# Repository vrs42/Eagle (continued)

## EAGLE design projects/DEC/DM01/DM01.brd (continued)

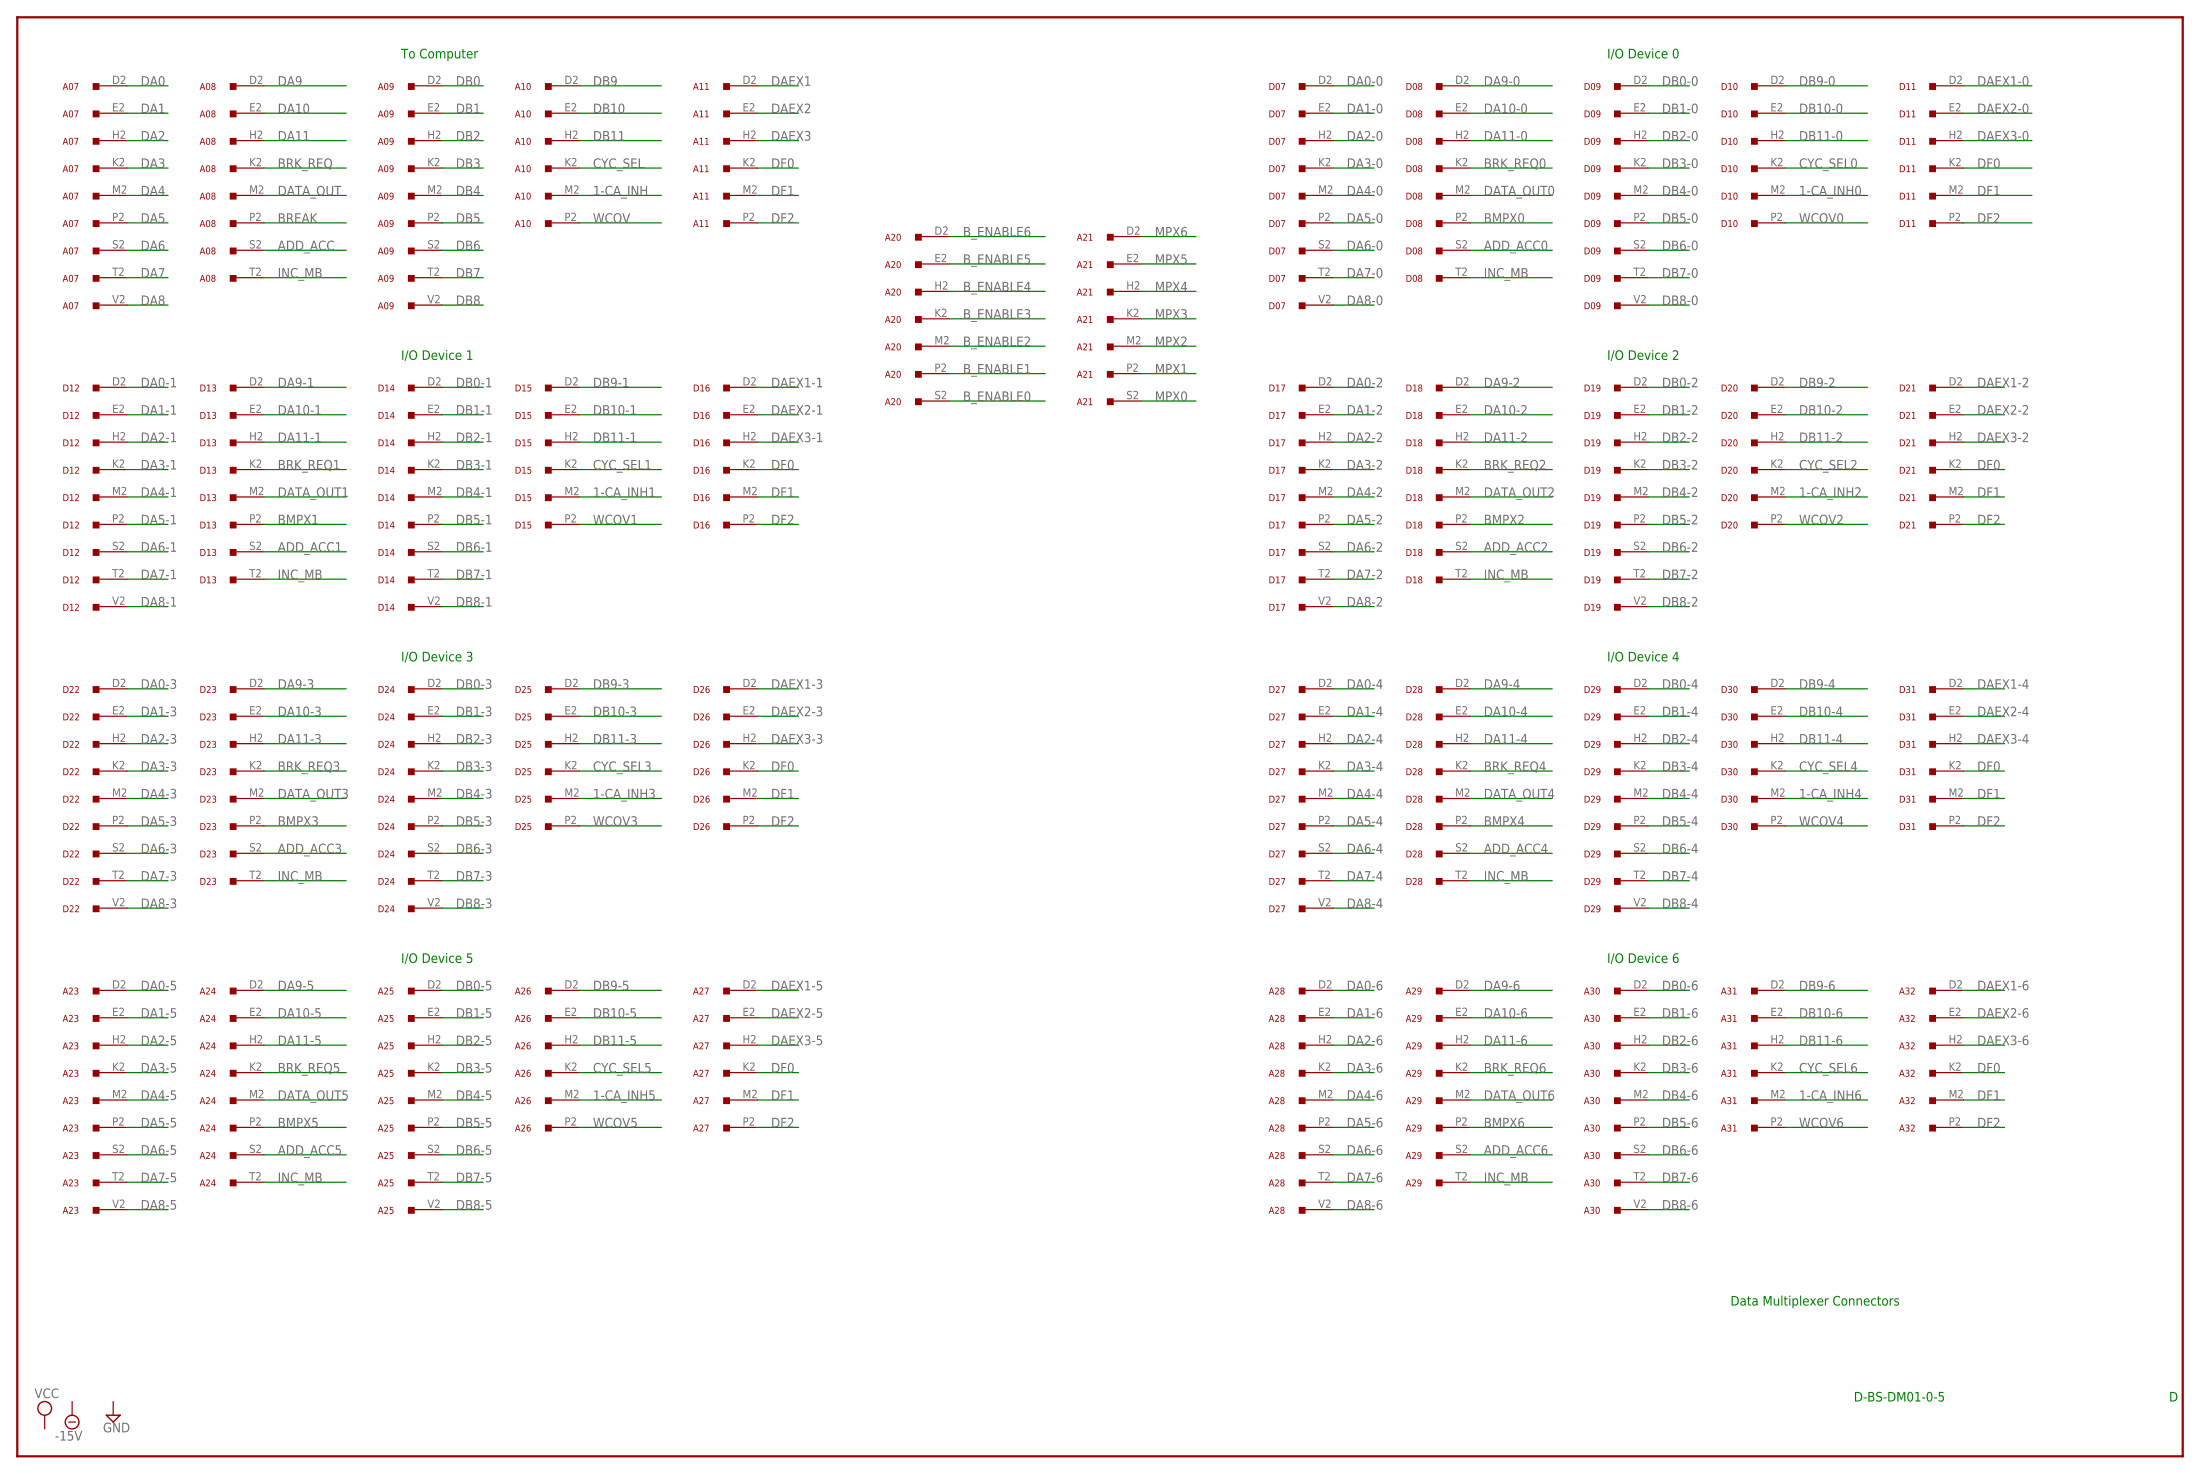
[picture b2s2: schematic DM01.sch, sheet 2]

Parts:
A07, A08, A09, A10, A11, A20, A21, A23, A24, A25, A26, A27, A28, A29, A30, A31, A32: W021S; H807S
D07, D08, D09, D10, D11, D12, D13, D14, D15, D16, D17, D18, D19, D20, D21, D22, D23, D24, D25, D26, D27, D28, D29, D30, D31: W021S; H807S

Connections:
1-CA_INH: A10.M2; also elsewhere on the board
1-CA_INH0: D10.M2; also elsewhere on the board
1-CA_INH1: D15.M2; also elsewhere on the board
1-CA_INH2: D20.M2; also elsewhere on the board
1-CA_INH3: D25.M2; also elsewhere on the board
1-CA_INH4: D30.M2; also elsewhere on the board
1-CA_INH5: A26.M2; also elsewhere on the board
1-CA_INH6: A31.M2; also elsewhere on the board
ADD_ACC: A08.S2; also elsewhere on the board
ADD_ACC0: D08.S2; also elsewhere on the board
ADD_ACC1: D13.S2; also elsewhere on the board
ADD_ACC2: D18.S2; also elsewhere on the board
ADD_ACC3: D23.S2; also elsewhere on the board
ADD_ACC4: D28.S2; also elsewhere on the board
ADD_ACC5: A24.S2; also elsewhere on the board
ADD_ACC6: A29.S2; also elsewhere on the board
BMPX0: D08.P2; also elsewhere on the board
BMPX1: D13.P2; also elsewhere on the board
BMPX2: D18.P2; also elsewhere on the board
BMPX3: D23.P2; also elsewhere on the board
BMPX4: D28.P2; also elsewhere on the board
BMPX5: A24.P2; also elsewhere on the board
BMPX6: A29.P2; also elsewhere on the board
BREAK: A08.P2; also elsewhere on the board
BRK_REQ: A08.K2; also elsewhere on the board
BRK_REQ0: D08.K2; also elsewhere on the board
BRK_REQ1: D13.K2; also elsewhere on the board
BRK_REQ2: D18.K2; also elsewhere on the board
BRK_REQ3: D23.K2; also elsewhere on the board
BRK_REQ4: D28.K2; also elsewhere on the board
BRK_REQ5: A24.K2; also elsewhere on the board
BRK_REQ6: A29.K2; also elsewhere on the board
B_ENABLE0: A20.S2; also elsewhere on the board
B_ENABLE1: A20.P2; also elsewhere on the board
B_ENABLE2: A20.M2; also elsewhere on the board
B_ENABLE3: A20.K2; also elsewhere on the board
B_ENABLE4: A20.H2; also elsewhere on the board
B_ENABLE5: A20.E2; also elsewhere on the board
B_ENABLE6: A20.D2; also elsewhere on the board
CYC_SEL: A10.K2; also elsewhere on the board
CYC_SEL0: D10.K2; also elsewhere on the board
CYC_SEL1: D15.K2; also elsewhere on the board
CYC_SEL2: D20.K2; also elsewhere on the board
CYC_SEL3: D25.K2; also elsewhere on the board
CYC_SEL4: D30.K2; also elsewhere on the board
CYC_SEL5: A26.K2; also elsewhere on the board
CYC_SEL6: A31.K2; also elsewhere on the board
DA0: A07.D2; also elsewhere on the board
DA0-0: D07.D2; also elsewhere on the board
DA0-1: D12.D2; also elsewhere on the board
DA0-2: D17.D2; also elsewhere on the board
DA0-3: D22.D2; also elsewhere on the board
DA0-4: D27.D2; also elsewhere on the board
DA0-5: A23.D2; also elsewhere on the board
DA0-6: A28.D2; also elsewhere on the board
DA1: A07.E2; also elsewhere on the board
DA1-0: D07.E2; also elsewhere on the board
DA1-1: D12.E2; also elsewhere on the board
DA1-2: D17.E2; also elsewhere on the board
DA1-3: D22.E2; also elsewhere on the board
DA1-4: D27.E2; also elsewhere on the board
DA1-5: A23.E2; also elsewhere on the board
DA1-6: A28.E2; also elsewhere on the board
DA2: A07.H2; also elsewhere on the board
DA2-0: D07.H2; also elsewhere on the board
DA2-1: D12.H2; also elsewhere on the board
DA2-2: D17.H2; also elsewhere on the board
DA2-3: D22.H2; also elsewhere on the board
DA2-4: D27.H2; also elsewhere on the board
DA2-5: A23.H2; also elsewhere on the board
DA2-6: A28.H2; also elsewhere on the board
DA3: A07.K2; also elsewhere on the board
DA3-0: D07.K2; also elsewhere on the board
DA3-1: D12.K2; also elsewhere on the board
DA3-2: D17.K2; also elsewhere on the board
DA3-3: D22.K2; also elsewhere on the board
DA3-4: D27.K2; also elsewhere on the board
DA3-5: A23.K2; also elsewhere on the board
DA3-6: A28.K2; also elsewhere on the board
DA4: A07.M2; also elsewhere on the board
DA4-0: D07.M2; also elsewhere on the board
DA4-1: D12.M2; also elsewhere on the board
DA4-2: D17.M2; also elsewhere on the board
DA4-3: D22.M2; also elsewhere on the board
DA4-4: D27.M2; also elsewhere on the board
DA4-5: A23.M2; also elsewhere on the board
DA4-6: A28.M2; also elsewhere on the board
DA5: A07.P2; also elsewhere on the board
DA5-0: D07.P2; also elsewhere on the board
DA5-1: D12.P2; also elsewhere on the board
DA5-2: D17.P2; also elsewhere on the board
DA5-3: D22.P2; also elsewhere on the board
DA5-4: D27.P2; also elsewhere on the board
DA5-5: A23.P2; also elsewhere on the board
DA5-6: A28.P2; also elsewhere on the board
DA6: A07.S2; also elsewhere on the board
DA6-0: D07.S2; also elsewhere on the board
DA6-1: D12.S2; also elsewhere on the board
DA6-2: D17.S2; also elsewhere on the board
DA6-3: D22.S2; also elsewhere on the board
DA6-4: D27.S2; also elsewhere on the board
DA6-5: A23.S2; also elsewhere on the board
DA6-6: A28.S2; also elsewhere on the board
DA7: A07.T2; also elsewhere on the board
DA7-0: D07.T2; also elsewhere on the board
DA7-1: D12.T2; also elsewhere on the board
DA7-2: D17.T2; also elsewhere on the board
DA7-3: D22.T2; also elsewhere on the board
DA7-4: D27.T2; also elsewhere on the board
DA7-5: A23.T2; also elsewhere on the board
DA7-6: A28.T2; also elsewhere on the board
DA8: A07.V2; also elsewhere on the board
DA8-0: D07.V2; also elsewhere on the board
DA8-1: D12.V2; also elsewhere on the board
DA8-2: D17.V2; also elsewhere on the board
DA8-3: D22.V2; also elsewhere on the board
DA8-4: D27.V2; also elsewhere on the board
DA8-5: A23.V2; also elsewhere on the board
DA8-6: A28.V2; also elsewhere on the board
DA9: A08.D2; also elsewhere on the board
DA9-0: D08.D2; also elsewhere on the board
DA9-1: D13.D2; also elsewhere on the board
DA9-2: D18.D2; also elsewhere on the board
DA9-3: D23.D2; also elsewhere on the board
DA9-4: D28.D2; also elsewhere on the board
DA9-5: A24.D2; also elsewhere on the board
DA9-6: A29.D2; also elsewhere on the board
DA10: A08.E2; also elsewhere on the board
DA10-0: D08.E2; also elsewhere on the board
DA10-1: D13.E2; also elsewhere on the board
DA10-2: D18.E2; also elsewhere on the board
DA10-3: D23.E2; also elsewhere on the board
DA10-4: D28.E2; also elsewhere on the board
DA10-5: A24.E2; also elsewhere on the board
DA10-6: A29.E2; also elsewhere on the board
DA11: A08.H2; also elsewhere on the board
DA11-0: D08.H2; also elsewhere on the board
DA11-1: D13.H2; also elsewhere on the board
DA11-2: D18.H2; also elsewhere on the board
DA11-3: D23.H2; also elsewhere on the board
DA11-4: D28.H2; also elsewhere on the board
DA11-5: A24.H2; also elsewhere on the board
DA11-6: A29.H2; also elsewhere on the board
DAEX1: A11.D2; also elsewhere on the board
DAEX1-0: D11.D2; also elsewhere on the board
DAEX1-1: D16.D2; also elsewhere on the board
DAEX1-2: D21.D2; also elsewhere on the board
DAEX1-3: D26.D2; also elsewhere on the board
DAEX1-4: D31.D2; also elsewhere on the board
DAEX1-5: A27.D2; also elsewhere on the board
DAEX1-6: A32.D2; also elsewhere on the board
DAEX2: A11.E2; also elsewhere on the board
DAEX2-0: D11.E2; also elsewhere on the board
DAEX2-1: D16.E2; also elsewhere on the board
DAEX2-2: D21.E2; also elsewhere on the board
DAEX2-3: D26.E2; also elsewhere on the board
DAEX2-4: D31.E2; also elsewhere on the board
DAEX2-5: A27.E2; also elsewhere on the board
DAEX2-6: A32.E2; also elsewhere on the board
DAEX3: A11.H2; also elsewhere on the board
DAEX3-0: D11.H2; also elsewhere on the board
DAEX3-1: D16.H2; also elsewhere on the board
DAEX3-2: D21.H2; also elsewhere on the board
DAEX3-3: D26.H2; also elsewhere on the board
DAEX3-4: D31.H2; also elsewhere on the board
DAEX3-5: A27.H2; also elsewhere on the board
DAEX3-6: A32.H2; also elsewhere on the board
DATA_OUT: A08.M2; also elsewhere on the board
DATA_OUT0: D08.M2; also elsewhere on the board
DATA_OUT1: D13.M2; also elsewhere on the board
DATA_OUT2: D18.M2; also elsewhere on the board
DATA_OUT3: D23.M2; also elsewhere on the board
DATA_OUT4: D28.M2; also elsewhere on the board
DATA_OUT5: A24.M2; also elsewhere on the board
DATA_OUT6: A29.M2; also elsewhere on the board
DB0: A09.D2; also elsewhere on the board
DB0-0: D09.D2; also elsewhere on the board
DB0-1: D14.D2; also elsewhere on the board
DB0-2: D19.D2; also elsewhere on the board
DB0-3: D24.D2; also elsewhere on the board
DB0-4: D29.D2; also elsewhere on the board
DB0-5: A25.D2; also elsewhere on the board
DB0-6: A30.D2; also elsewhere on the board
DB1: A09.E2; also elsewhere on the board
DB1-0: D09.E2; also elsewhere on the board
DB1-1: D14.E2; also elsewhere on the board
DB1-2: D19.E2; also elsewhere on the board
DB1-3: D24.E2; also elsewhere on the board
DB1-4: D29.E2; also elsewhere on the board
DB1-5: A25.E2; also elsewhere on the board
DB1-6: A30.E2; also elsewhere on the board
DB2: A09.H2; also elsewhere on the board
DB2-0: D09.H2; also elsewhere on the board
DB2-1: D14.H2; also elsewhere on the board
DB2-2: D19.H2; also elsewhere on the board
DB2-3: D24.H2; also elsewhere on the board
DB2-4: D29.H2; also elsewhere on the board
DB2-5: A25.H2; also elsewhere on the board
DB2-6: A30.H2; also elsewhere on the board
DB3: A09.K2; also elsewhere on the board
DB3-0: D09.K2; also elsewhere on the board
DB3-1: D14.K2; also elsewhere on the board
DB3-2: D19.K2; also elsewhere on the board
DB3-3: D24.K2; also elsewhere on the board
DB3-4: D29.K2; also elsewhere on the board
DB3-5: A25.K2; also elsewhere on the board
DB3-6: A30.K2; also elsewhere on the board
DB4: A09.M2; also elsewhere on the board
DB4-0: D09.M2; also elsewhere on the board
DB4-1: D14.M2; also elsewhere on the board
DB4-2: D19.M2; also elsewhere on the board
DB4-3: D24.M2; also elsewhere on the board
DB4-4: D29.M2; also elsewhere on the board
DB4-5: A25.M2; also elsewhere on the board
DB4-6: A30.M2; also elsewhere on the board
DB5: A09.P2; also elsewhere on the board
DB5-0: D09.P2; also elsewhere on the board
DB5-1: D14.P2; also elsewhere on the board
DB5-2: D19.P2; also elsewhere on the board
DB5-3: D24.P2; also elsewhere on the board
DB5-4: D29.P2; also elsewhere on the board
DB5-5: A25.P2; also elsewhere on the board
DB5-6: A30.P2; also elsewhere on the board
DB6: A09.S2; also elsewhere on the board
DB6-0: D09.S2; also elsewhere on the board
DB6-1: D14.S2; also elsewhere on the board
DB6-2: D19.S2; also elsewhere on the board
DB6-3: D24.S2; also elsewhere on the board
DB6-4: D29.S2; also elsewhere on the board
DB6-5: A25.S2; also elsewhere on the board
DB6-6: A30.S2; also elsewhere on the board
DB7: A09.T2; also elsewhere on the board
DB7-0: D09.T2; also elsewhere on the board
DB7-1: D14.T2; also elsewhere on the board
DB7-2: D19.T2; also elsewhere on the board
DB7-3: D24.T2; also elsewhere on the board
DB7-4: D29.T2; also elsewhere on the board
DB7-5: A25.T2; also elsewhere on the board
DB7-6: A30.T2; also elsewhere on the board
DB8: A09.V2; also elsewhere on the board
DB8-0: D09.V2; also elsewhere on the board
DB8-1: D14.V2; also elsewhere on the board
DB8-2: D19.V2; also elsewhere on the board
DB8-3: D24.V2; also elsewhere on the board
DB8-4: D29.V2; also elsewhere on the board
DB8-5: A25.V2; also elsewhere on the board
DB8-6: A30.V2; also elsewhere on the board
DB9: A10.D2; also elsewhere on the board
DB9-0: D10.D2; also elsewhere on the board
DB9-1: D15.D2; also elsewhere on the board
DB9-2: D20.D2; also elsewhere on the board
DB9-3: D25.D2; also elsewhere on the board
DB9-4: D30.D2; also elsewhere on the board
DB9-5: A26.D2; also elsewhere on the board
DB9-6: A31.D2; also elsewhere on the board
DB10: A10.E2; also elsewhere on the board
DB10-0: D10.E2; also elsewhere on the board
DB10-1: D15.E2; also elsewhere on the board
DB10-2: D20.E2; also elsewhere on the board
DB10-3: D25.E2; also elsewhere on the board
DB10-4: D30.E2; also elsewhere on the board
DB10-5: A26.E2; also elsewhere on the board
DB10-6: A31.E2; also elsewhere on the board
DB11: A10.H2; also elsewhere on the board
DB11-0: D10.H2; also elsewhere on the board
DB11-1: D15.H2; also elsewhere on the board
DB11-2: D20.H2; also elsewhere on the board
DB11-3: D25.H2; also elsewhere on the board
DB11-4: D30.H2; also elsewhere on the board
DB11-5: A26.H2; also elsewhere on the board
DB11-6: A31.H2; also elsewhere on the board
DF0: A11.K2, A27.K2, A32.K2, D11.K2, D16.K2, D21.K2, D26.K2, D31.K2
DF1: A11.M2, A27.M2, A32.M2, D11.M2, D16.M2, D21.M2, D26.M2, D31.M2
DF2: A11.P2, A27.P2, A32.P2, D11.P2, D16.P2, D21.P2, D26.P2, D31.P2
GND: A07.C2 (GND), A07.F2 (GND), A07.J2 (GND), A07.L2 (GND), A07.N2 (GND), A07.R2 (GND), A07.U2 (GND), A08.C2 (GND), A08.F2 (GND), A08.J2 (GND), A08.L2 (GND), A08.N2 (GND), A08.R2 (GND), A08.U2 (GND), A09.C2 (GND), A09.F2 (GND), A09.J2 (GND), A09.L2 (GND), A09.N2 (GND), A09.R2 (GND), A09.U2 (GND), A10.C2 (GND), A10.F2 (GND), A10.J2 (GND), A10.L2 (GND), A10.N2 (GND), A10.R2 (GND), A10.U2 (GND), A11.C2 (GND), A11.F2 (GND), A11.J2 (GND), A11.L2 (GND), A11.N2 (GND), A11.R2 (GND), A11.U2 (GND), A20.C2 (GND), A20.F2 (GND), A20.J2 (GND), A20.L2 (GND), A20.N2 (GND), A20.R2 (GND), A20.U2 (GND), A21.C2 (GND), A21.F2 (GND), A21.J2 (GND), A21.L2 (GND), A21.N2 (GND), A21.R2 (GND), A21.U2 (GND), A23.C2 (GND), A23.F2 (GND), A23.J2 (GND), A23.L2 (GND), A23.N2 (GND), A23.R2 (GND), A23.U2 (GND), A24.C2 (GND), A24.F2 (GND), A24.J2 (GND), A24.L2 (GND), A24.N2 (GND), A24.R2 (GND), A24.U2 (GND), A25.C2 (GND), A25.F2 (GND), A25.J2 (GND), A25.L2 (GND), A25.N2 (GND), A25.R2 (GND), A25.U2 (GND), A26.C2 (GND), A26.F2 (GND), A26.J2 (GND), A26.L2 (GND), A26.N2 (GND), A26.R2 (GND), A26.U2 (GND), A27.C2 (GND), A27.F2 (GND), A27.J2 (GND), A27.L2 (GND), A27.N2 (GND), A27.R2 (GND), A27.U2 (GND), A28.C2 (GND), A28.F2 (GND), A28.J2 (GND), A28.L2 (GND), A28.N2 (GND), A28.R2 (GND), A28.U2 (GND), A29.C2 (GND), A29.F2 (GND), A29.J2 (GND), A29.L2 (GND), A29.N2 (GND), A29.R2 (GND), A29.U2 (GND), A30.C2 (GND), A30.F2 (GND), A30.J2 (GND), A30.L2 (GND), A30.N2 (GND), A30.R2 (GND), A30.U2 (GND), A31.C2 (GND), A31.F2 (GND), A31.J2 (GND), A31.L2 (GND), A31.N2 (GND), A31.R2 (GND), A31.U2 (GND), A32.C2 (GND), A32.F2 (GND), A32.J2 (GND), A32.L2 (GND), A32.N2 (GND), A32.R2 (GND), A32.U2 (GND), D07.C2 (GND), D07.F2 (GND), D07.J2 (GND), D07.L2 (GND), D07.N2 (GND), D07.R2 (GND), D07.U2 (GND), D08.C2 (GND), D08.F2 (GND), D08.J2 (GND), D08.L2 (GND), D08.N2 (GND), D08.R2 (GND), D08.U2 (GND), D09.C2 (GND), D09.F2 (GND), D09.J2 (GND), D09.L2 (GND), D09.N2 (GND), D09.R2 (GND), D09.U2 (GND), D10.C2 (GND), D10.F2 (GND), D10.J2 (GND), D10.L2 (GND), D10.N2 (GND), D10.R2 (GND), D10.U2 (GND), D11.C2 (GND), D11.F2 (GND), D11.J2 (GND), D11.L2 (GND), D11.N2 (GND), D11.R2 (GND), D11.U2 (GND), D12.C2 (GND), D12.F2 (GND), D12.J2 (GND), D12.L2 (GND), D12.N2 (GND), D12.R2 (GND), D12.U2 (GND), D13.C2 (GND), D13.F2 (GND), D13.J2 (GND), D13.L2 (GND), D13.N2 (GND), D13.R2 (GND), D13.U2 (GND), D14.C2 (GND), D14.F2 (GND), D14.J2 (GND), D14.L2 (GND), D14.N2 (GND), D14.R2 (GND), D14.U2 (GND), D15.C2 (GND), D15.F2 (GND), D15.J2 (GND), D15.L2 (GND), D15.N2 (GND), D15.R2 (GND), D15.U2 (GND), D16.C2 (GND), D16.F2 (GND), D16.J2 (GND), D16.L2 (GND), D16.N2 (GND), D16.R2 (GND), D16.U2 (GND), D17.C2 (GND), D17.F2 (GND), D17.J2 (GND), D17.L2 (GND), D17.N2 (GND), D17.R2 (GND), D17.U2 (GND), D18.C2 (GND), D18.F2 (GND), D18.J2 (GND), D18.L2 (GND), D18.N2 (GND), D18.R2 (GND), D18.U2 (GND), D19.C2 (GND), D19.F2 (GND), D19.J2 (GND), D19.L2 (GND), D19.N2 (GND), D19.R2 (GND), D19.U2 (GND), D20.C2 (GND), D20.F2 (GND), D20.J2 (GND), D20.L2 (GND), D20.N2 (GND), D20.R2 (GND), D20.U2 (GND), D21.C2 (GND), D21.F2 (GND), D21.J2 (GND), D21.L2 (GND), D21.N2 (GND), D21.R2 (GND), D21.U2 (GND), D22.C2 (GND), D22.F2 (GND), D22.J2 (GND), D22.L2 (GND), D22.N2 (GND), D22.R2 (GND), D22.U2 (GND), D23.C2 (GND), D23.F2 (GND), D23.J2 (GND), D23.L2 (GND), D23.N2 (GND), D23.R2 (GND), D23.U2 (GND), D24.C2 (GND), D24.F2 (GND), D24.J2 (GND), D24.L2 (GND), D24.N2 (GND), D24.R2 (GND), D24.U2 (GND), D25.C2 (GND), D25.F2 (GND), D25.J2 (GND), D25.L2 (GND), D25.N2 (GND), D25.R2 (GND), D25.U2 (GND), D26.C2 (GND), D26.F2 (GND), D26.J2 (GND), D26.L2 (GND), D26.N2 (GND), D26.R2 (GND), D26.U2 (GND), D27.C2 (GND), D27.F2 (GND), D27.J2 (GND), D27.L2 (GND), D27.N2 (GND), D27.R2 (GND), D27.U2 (GND), D28.C2 (GND), D28.F2 (GND), D28.J2 (GND), D28.L2 (GND), D28.N2 (GND), D28.R2 (GND), D28.U2 (GND), D29.C2 (GND), D29.F2 (GND), D29.J2 (GND), D29.L2 (GND), D29.N2 (GND), D29.R2 (GND), D29.U2 (GND), D30.C2 (GND), D30.F2 (GND), D30.J2 (GND), D30.L2 (GND), D30.N2 (GND), D30.R2 (GND), D30.U2 (GND), D31.C2 (GND), D31.F2 (GND), D31.J2 (GND), D31.L2 (GND), D31.N2 (GND), D31.R2 (GND), D31.U2 (GND); also elsewhere on the board
INC_MB: A08.T2, A24.T2, A29.T2, D08.T2, D13.T2, D18.T2, D23.T2, D28.T2
MPX0: A21.S2; also elsewhere on the board
MPX1: A21.P2; also elsewhere on the board
MPX2: A21.M2; also elsewhere on the board
MPX3: A21.K2; also elsewhere on the board
MPX4: A21.H2; also elsewhere on the board
MPX5: A21.E2; also elsewhere on the board
MPX6: A21.D2; also elsewhere on the board
WCOV: A10.P2; also elsewhere on the board
WCOV0: D10.P2; also elsewhere on the board
WCOV1: D15.P2; also elsewhere on the board
WCOV2: D20.P2; also elsewhere on the board
WCOV3: D25.P2; also elsewhere on the board
WCOV4: D30.P2; also elsewhere on the board
WCOV5: A26.P2; also elsewhere on the board
WCOV6: A31.P2; also elsewhere on the board

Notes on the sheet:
D-BS-DM01-0-5
Data Multiplexer Connectors
To Computer
I/O Device 0
I/O Device 2
I/O Device 1
I/O Device 3
I/O Device 4
I/O Device 5
I/O Device 6

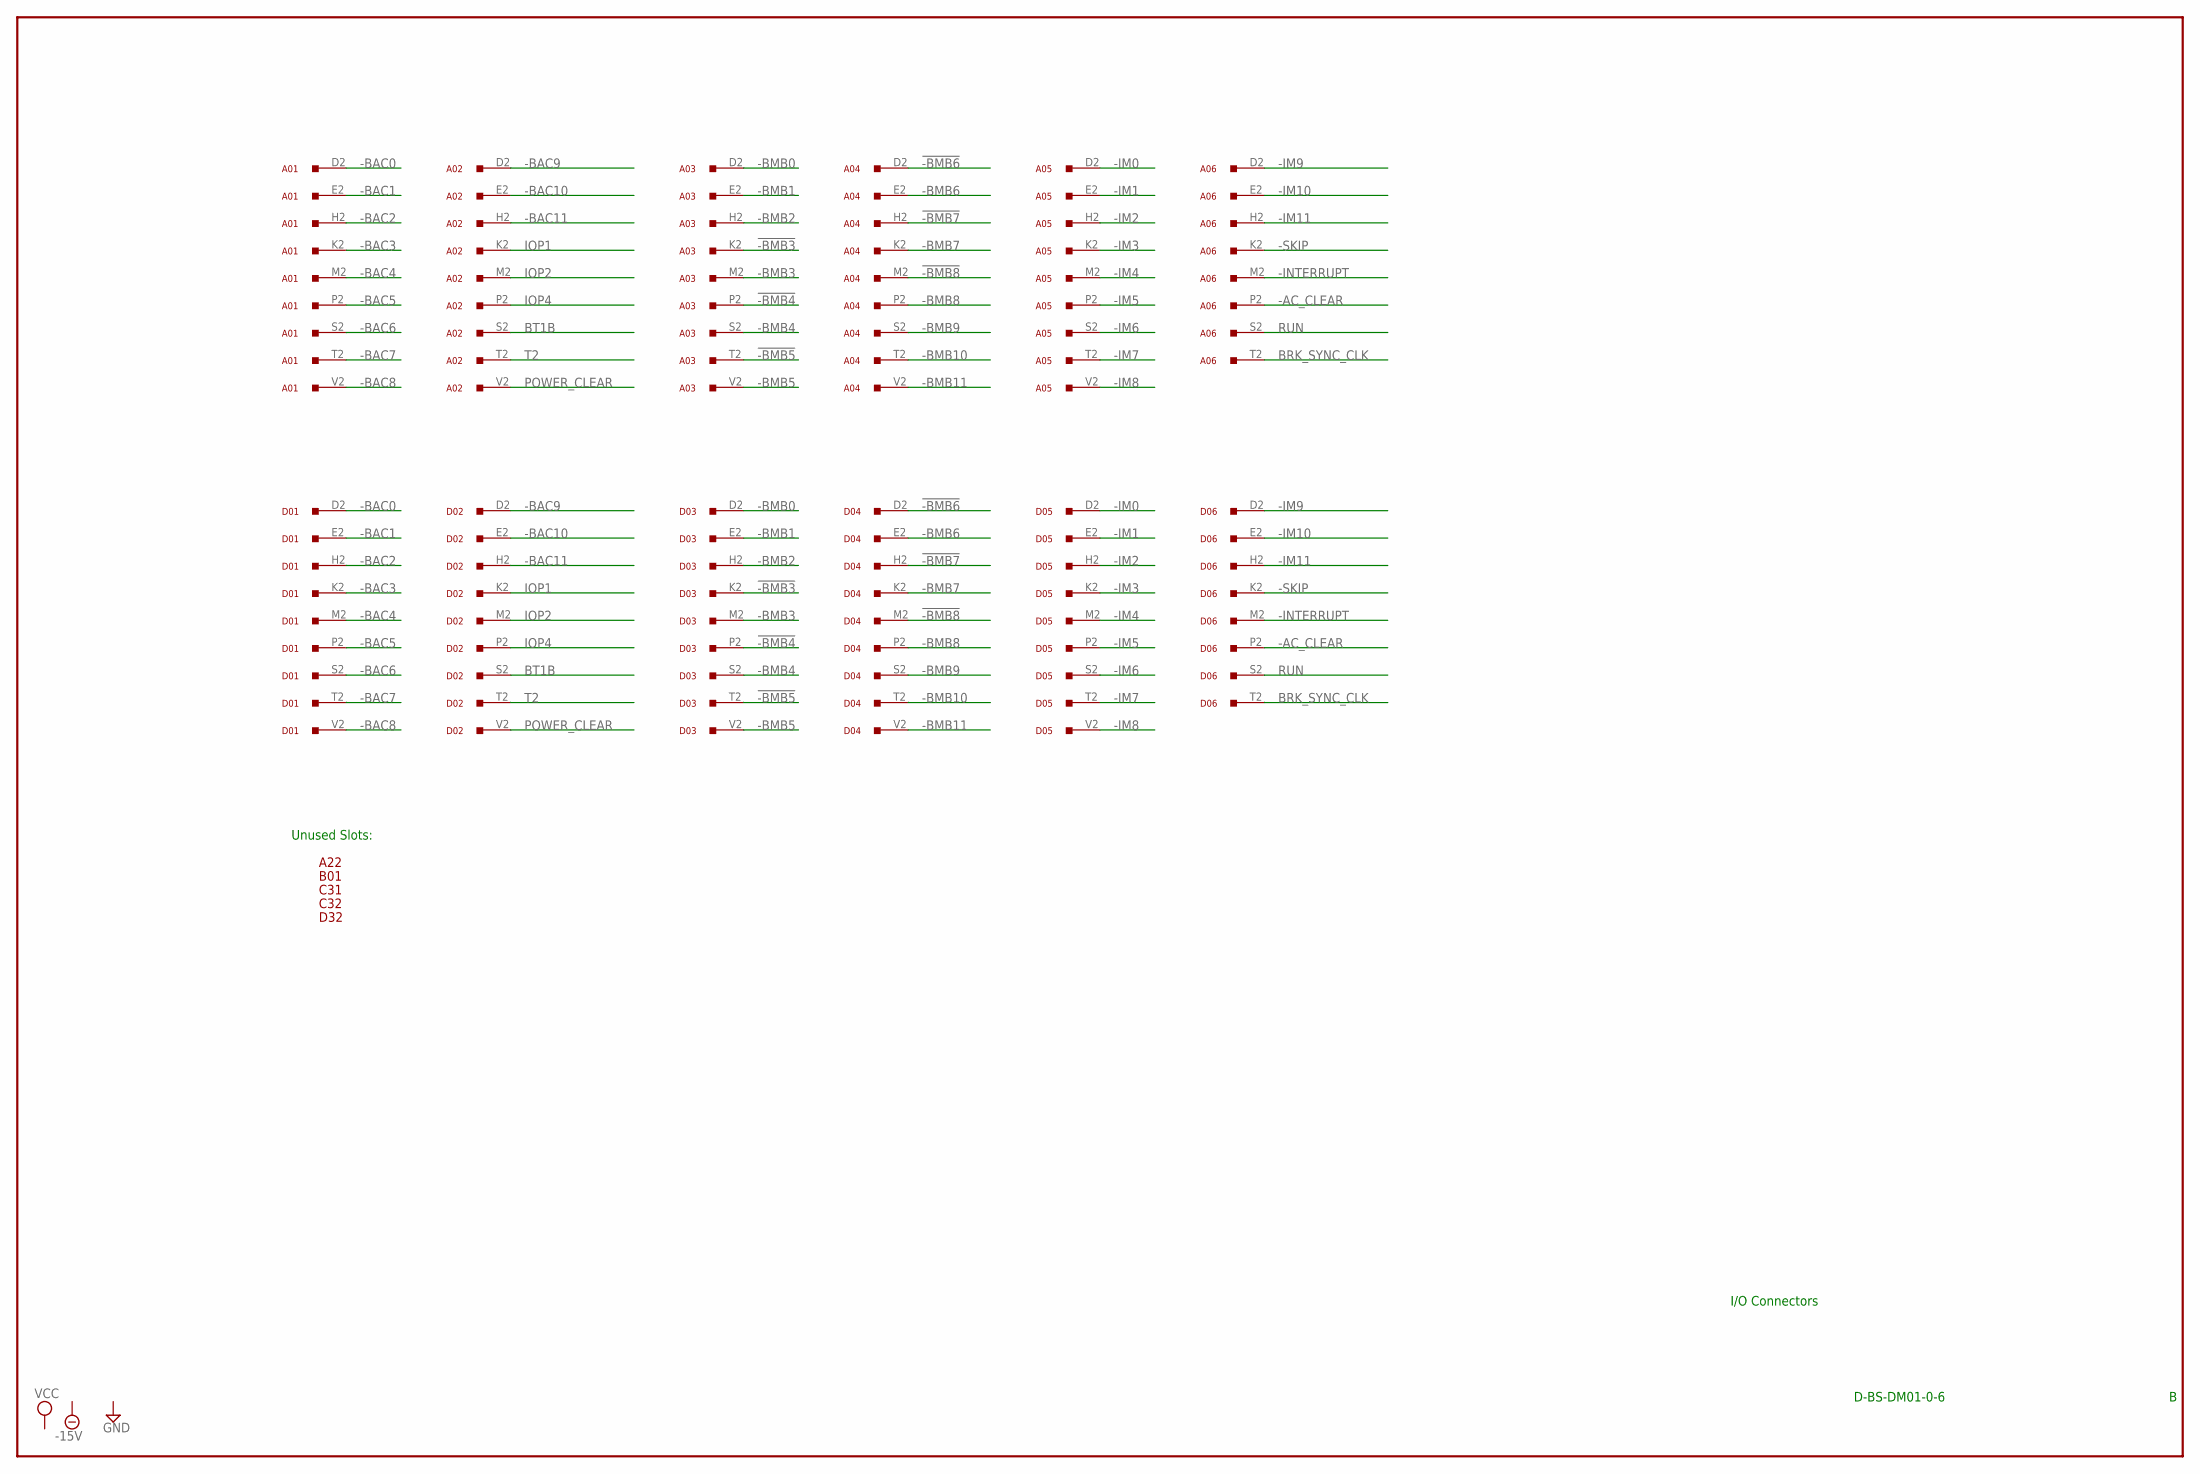
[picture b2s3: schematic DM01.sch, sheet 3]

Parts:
A01, A02, A03, A04, A05, A06: W021S; H807S
A22: EMPTYS; H807S
B01: EMPTYS; H807S
C31, C32: EMPTYS; H807S
D01, D02, D03, D04, D05, D06: W021S; H807S
D32: EMPTYS; H807S

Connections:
!-BMB3: A03.K2, D03.K2
!-BMB4: A03.P2, D03.P2
!-BMB5: A03.T2, D03.T2
!-BMB6: A04.D2, D04.D2
!-BMB7: A04.H2, D04.H2
!-BMB8: A04.M2, D04.M2
-15V: A22.B2 (-15V), B01.B2 (-15V), C31.B2 (-15V), C32.B2 (-15V), D32.B2 (-15V); also elsewhere on the board
-AC_CLEAR: A06.P2, D06.P2
-BAC0: A01.D2, D01.D2
-BAC1: A01.E2, D01.E2
-BAC2: A01.H2, D01.H2
-BAC3: A01.K2, D01.K2
-BAC4: A01.M2, D01.M2
-BAC5: A01.P2, D01.P2
-BAC6: A01.S2, D01.S2
-BAC7: A01.T2, D01.T2
-BAC8: A01.V2, D01.V2
-BAC9: A02.D2, D02.D2
-BAC10: A02.E2, D02.E2
-BAC11: A02.H2, D02.H2
-BMB0: A03.D2, D03.D2
-BMB1: A03.E2, D03.E2
-BMB2: A03.H2, D03.H2
-BMB3: A03.M2, D03.M2
-BMB4: A03.S2, D03.S2
-BMB5: A03.V2, D03.V2
-BMB6: A04.E2, D04.E2
-BMB7: A04.K2, D04.K2
-BMB8: A04.P2, D04.P2
-BMB9: A04.S2, D04.S2
-BMB10: A04.T2, D04.T2
-BMB11: A04.V2, D04.V2
-IM0: A05.D2, D05.D2
-IM1: A05.E2, D05.E2
-IM2: A05.H2, D05.H2
-IM3: A05.K2, D05.K2
-IM4: A05.M2, D05.M2
-IM5: A05.P2, D05.P2
-IM6: A05.S2, D05.S2
-IM7: A05.T2, D05.T2
-IM8: A05.V2, D05.V2
-IM9: A06.D2, D06.D2
-IM10: A06.E2, D06.E2
-IM11: A06.H2, D06.H2
-INTERRUPT: A06.M2, D06.M2
-SKIP: A06.K2, D06.K2
BRK_SYNC_CLK: A06.T2, D06.T2; also elsewhere on the board
BT1B: A02.S2, D02.S2; also elsewhere on the board
GND: A01.C2 (GND), A01.F2 (GND), A01.J2 (GND), A01.L2 (GND), A01.N2 (GND), A01.R2 (GND), A01.U2 (GND), A02.C2 (GND), A02.F2 (GND), A02.J2 (GND), A02.L2 (GND), A02.N2 (GND), A02.R2 (GND), A02.U2 (GND), A03.C2 (GND), A03.F2 (GND), A03.J2 (GND), A03.L2 (GND), A03.N2 (GND), A03.R2 (GND), A03.U2 (GND), A04.C2 (GND), A04.F2 (GND), A04.J2 (GND), A04.L2 (GND), A04.N2 (GND), A04.R2 (GND), A04.U2 (GND), A05.C2 (GND), A05.F2 (GND), A05.J2 (GND), A05.L2 (GND), A05.N2 (GND), A05.R2 (GND), A05.U2 (GND), A06.C2 (GND), A06.F2 (GND), A06.J2 (GND), A06.L2 (GND), A06.N2 (GND), A06.R2 (GND), A06.U2 (GND), A22.C2 (GND), B01.C2 (GND), C31.C2 (GND), C32.C2 (GND), D01.C2 (GND), D01.F2 (GND), D01.J2 (GND), D01.L2 (GND), D01.N2 (GND), D01.R2 (GND), D01.U2 (GND), D02.C2 (GND), D02.F2 (GND), D02.J2 (GND), D02.L2 (GND), D02.N2 (GND), D02.R2 (GND), D02.U2 (GND), D03.C2 (GND), D03.F2 (GND), D03.J2 (GND), D03.L2 (GND), D03.N2 (GND), D03.R2 (GND), D03.U2 (GND), D04.C2 (GND), D04.F2 (GND), D04.J2 (GND), D04.L2 (GND), D04.N2 (GND), D04.R2 (GND), D04.U2 (GND), D05.C2 (GND), D05.F2 (GND), D05.J2 (GND), D05.L2 (GND), D05.N2 (GND), D05.R2 (GND), D05.U2 (GND), D06.C2 (GND), D06.F2 (GND), D06.J2 (GND), D06.L2 (GND), D06.N2 (GND), D06.R2 (GND), D06.U2 (GND), D32.C2 (GND); also elsewhere on the board
IOP1: A02.K2, D02.K2
IOP2: A02.M2, D02.M2
IOP4: A02.P2, D02.P2
POWER_CLEAR: A02.V2, D02.V2; also elsewhere on the board
RUN: A06.S2, D06.S2
T2: A02.T2, D02.T2; also elsewhere on the board
VCC: A22.A2 (VCC), B01.A2 (VCC), C31.A2 (VCC), C32.A2 (VCC), D32.A2 (VCC); also elsewhere on the board

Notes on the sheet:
D-BS-DM01-0-6
I/O Connectors
Unused Slots:

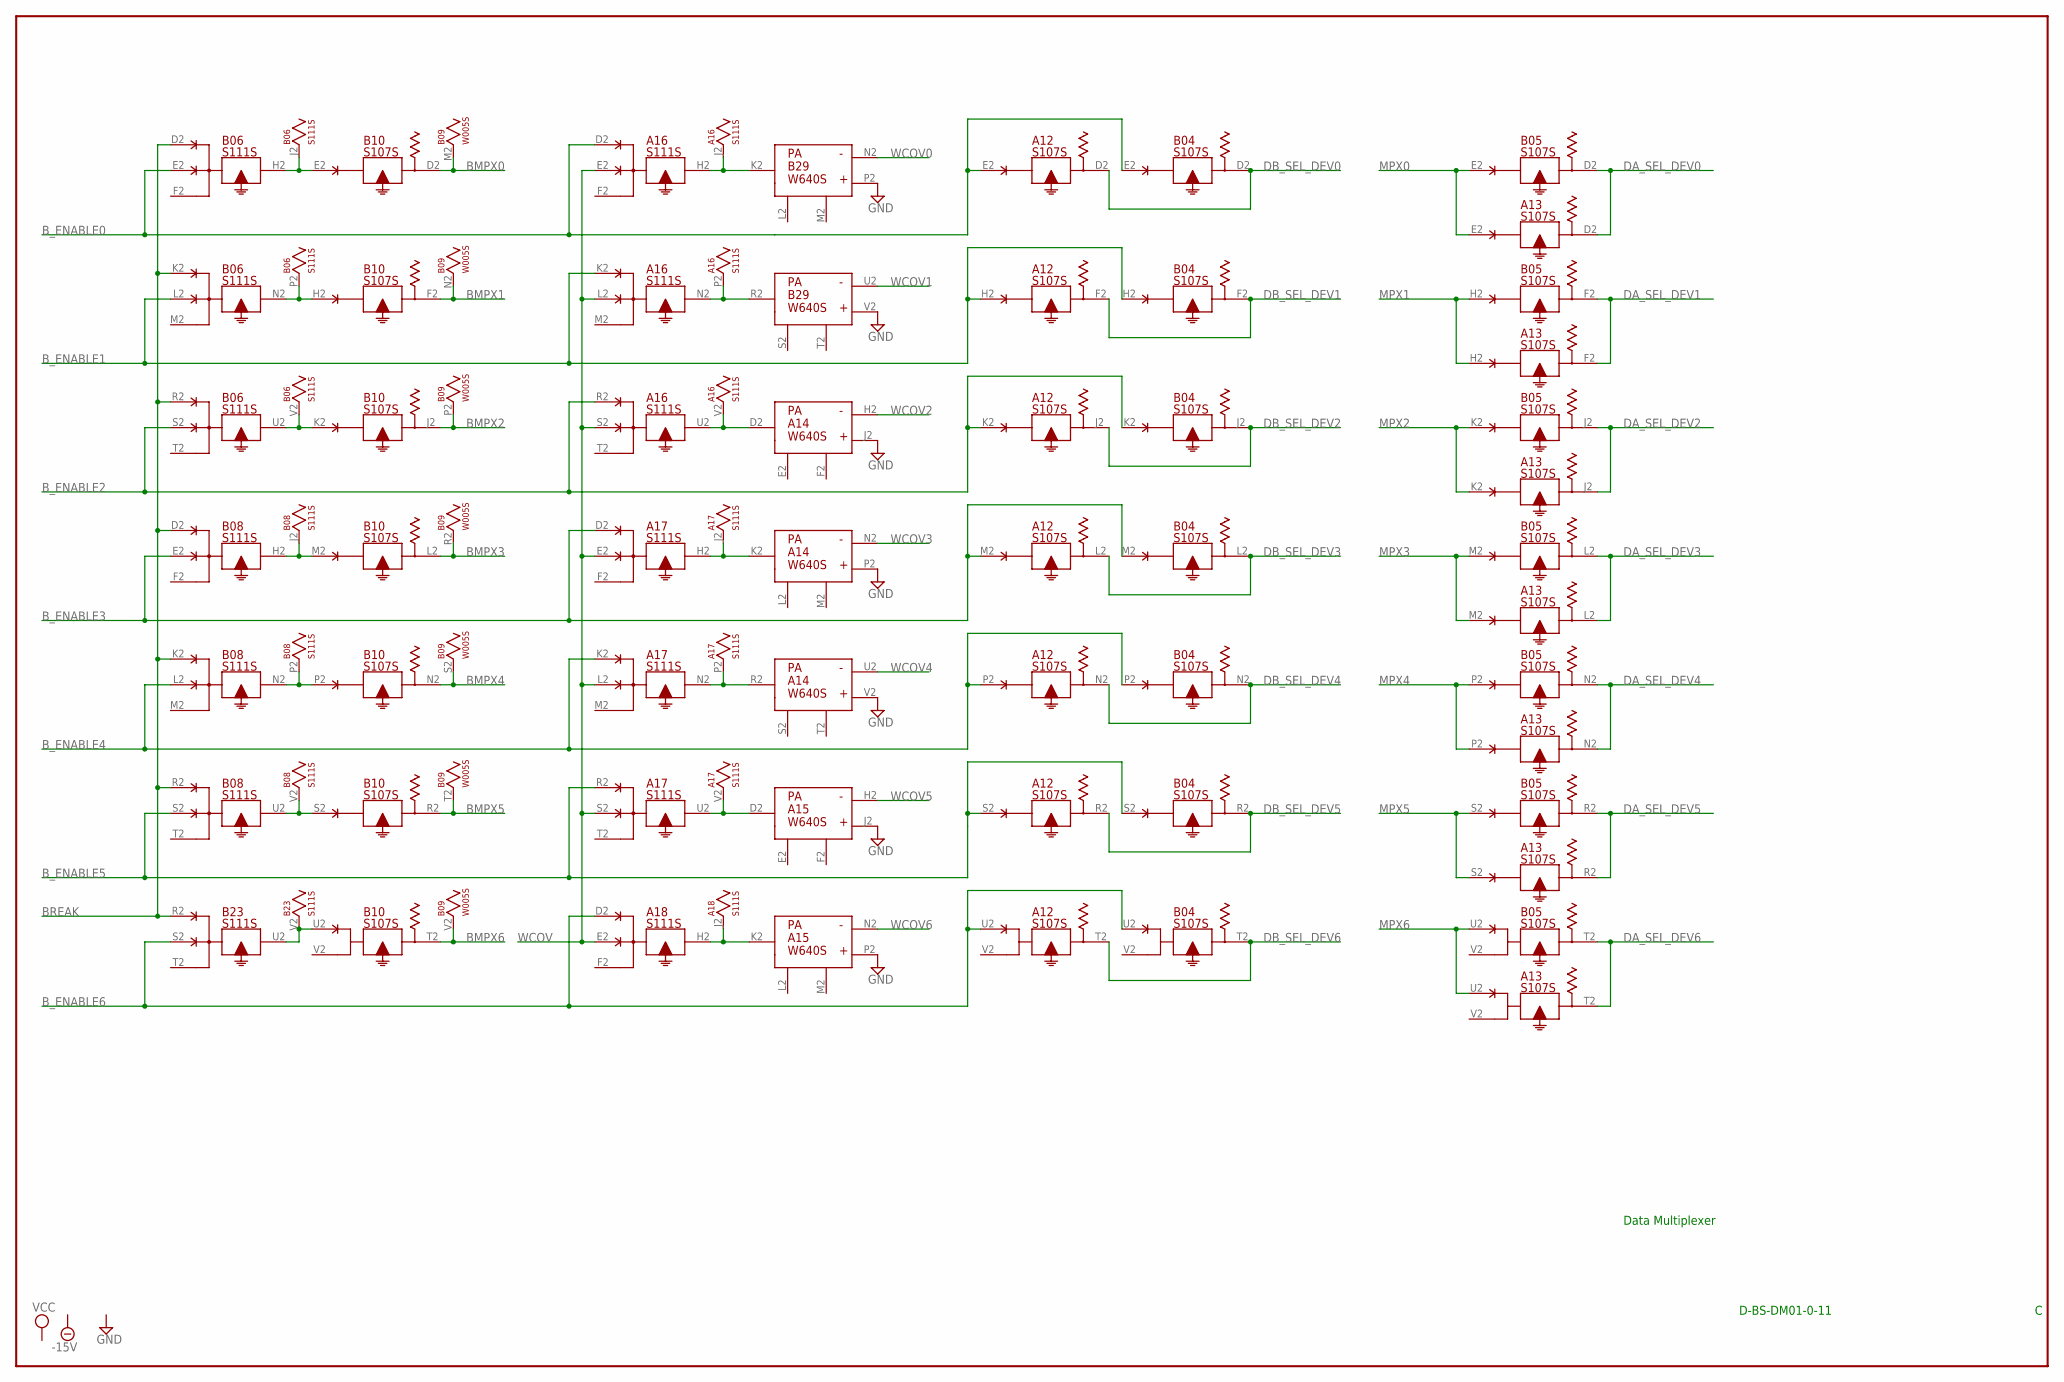
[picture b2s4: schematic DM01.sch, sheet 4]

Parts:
A12, A13: S107S; H807S
A14, A15: W640S; H807S
A16, A17, A18: S111S; H807S
B04, B05, B10: S107S; H807S
B06, B08, B23: S111S; H807S
B09: W005S; H807S
B29: W640S; H807S

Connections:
-15V: A12.B2 (-15V), A13.B2 (-15V), A14.B2 (-15V), A15.B2 (-15V), A16.B2 (-15V), A17.B2 (-15V), A18.B2 (-15V), B04.B2 (-15V), B05.B2 (-15V), B06.B2 (-15V), B08.B2 (-15V), B09.B2 (-15V), B10.B2 (-15V), B23.B2 (-15V), B29.B2 (-15V); also elsewhere on the board
BMPX0: B09.M2, B10.D2; also elsewhere on the board
BMPX1: B09.N2, B10.F2; also elsewhere on the board
BMPX2: B09.P2, B10.J2; also elsewhere on the board
BMPX3: B09.R2, B10.L2; also elsewhere on the board
BMPX4: B09.S2, B10.N2; also elsewhere on the board
BMPX5: B09.T2, B10.R2; also elsewhere on the board
BMPX6: B09.V2, B10.T2; also elsewhere on the board
BREAK: B06.D2, B06.K2, B06.R2, B08.D2, B08.K2, B08.R2, B23.R2; also elsewhere on the board
B_ENABLE0: A12.E2, A16.D2, B04.E2, B06.E2; also elsewhere on the board
B_ENABLE1: A12.H2, A16.K2, B04.H2, B06.L2; also elsewhere on the board
B_ENABLE2: A12.K2, A16.R2, B04.K2, B06.S2; also elsewhere on the board
B_ENABLE3: A12.M2, A17.D2, B04.M2, B08.E2; also elsewhere on the board
B_ENABLE4: A12.P2, A17.K2, B04.P2, B08.L2; also elsewhere on the board
B_ENABLE5: A12.S2, A17.R2, B04.S2, B08.S2; also elsewhere on the board
B_ENABLE6: A12.U2, A18.D2, B04.U2, B23.S2; also elsewhere on the board
DA_SEL_DEV0: A13.D2, B05.D2; also elsewhere on the board
DA_SEL_DEV1: A13.F2, B05.F2; also elsewhere on the board
DA_SEL_DEV2: A13.J2, B05.J2; also elsewhere on the board
DA_SEL_DEV3: A13.L2, B05.L2; also elsewhere on the board
DA_SEL_DEV4: A13.N2, B05.N2; also elsewhere on the board
DA_SEL_DEV5: A13.R2, B05.R2; also elsewhere on the board
DA_SEL_DEV6: A13.T2, B05.T2; also elsewhere on the board
DB_SEL_DEV0: A12.D2, B04.D2; also elsewhere on the board
DB_SEL_DEV1: A12.F2, B04.F2; also elsewhere on the board
DB_SEL_DEV2: A12.J2, B04.J2; also elsewhere on the board
DB_SEL_DEV3: A12.L2, B04.L2; also elsewhere on the board
DB_SEL_DEV4: A12.N2, B04.N2; also elsewhere on the board
DB_SEL_DEV5: A12.R2, B04.R2; also elsewhere on the board
DB_SEL_DEV6: A12.T2, B04.T2; also elsewhere on the board
GND: A12.C2 (GND), A13.C2 (GND), A14.C2 (GND), A14.J2 (J), A14.P2 (J), A14.V2 (J), A15.C2 (GND), A15.J2 (J), A15.P2 (J), A16.C2 (GND), A17.C2 (GND), A18.C2 (GND), B04.C2 (GND), B05.C2 (GND), B06.C2 (GND), B08.C2 (GND), B09.C2 (GND), B10.C2 (GND), B23.C2 (GND), B29.C2 (GND), B29.P2 (J), B29.V2 (J); also elsewhere on the board
MPX0: A13.E2, B05.E2; also elsewhere on the board
MPX1: A13.H2, B05.H2; also elsewhere on the board
MPX2: A13.K2, B05.K2; also elsewhere on the board
MPX3: A13.M2, B05.M2; also elsewhere on the board
MPX4: A13.P2, B05.P2; also elsewhere on the board
MPX5: A13.S2, B05.S2; also elsewhere on the board
MPX6: A13.U2, B05.U2; also elsewhere on the board
unnamed: A16.H2, A16.J2, B29.K2 (D)
unnamed: A16.N2, A16.P2, B29.R2 (D)
unnamed: A14.D2 (D), A16.U2, A16.V2
unnamed: A14.K2 (D), A17.H2, A17.J2
unnamed: A14.R2 (D), A17.N2, A17.P2
unnamed: A15.D2 (D), A17.U2, A17.V2
unnamed: A15.K2 (D), A18.H2, A18.J2
unnamed: B06.H2, B06.J2, B10.E2
unnamed: B06.N2, B06.P2, B10.H2
unnamed: B10.U2, B23.U2, B23.V2
unnamed: B08.U2, B08.V2, B10.S2
unnamed: B08.N2, B08.P2, B10.P2
unnamed: B08.H2, B08.J2, B10.M2
unnamed: B06.U2, B06.V2, B10.K2
VCC: A12.A2 (VCC), A13.A2 (VCC), A14.A2 (VCC), A15.A2 (VCC), A16.A2 (VCC), A17.A2 (VCC), A18.A2 (VCC), B04.A2 (VCC), B05.A2 (VCC), B06.A2 (VCC), B08.A2 (VCC), B09.A2 (VCC), B10.A2 (VCC), B23.A2 (VCC), B29.A2 (VCC); also elsewhere on the board
WCOV: A16.E2, A16.L2, A16.S2, A17.E2, A17.L2, A17.S2, A18.E2; also elsewhere on the board
WCOV0: B29.N2 (H); also elsewhere on the board
WCOV1: B29.U2 (H); also elsewhere on the board
WCOV2: A14.H2 (H); also elsewhere on the board
WCOV3: A14.N2 (H); also elsewhere on the board
WCOV4: A14.U2 (H); also elsewhere on the board
WCOV5: A15.H2 (H); also elsewhere on the board
WCOV6: A15.N2 (H); also elsewhere on the board

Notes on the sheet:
D-BS-DM01-0-11
Data Multiplexer
